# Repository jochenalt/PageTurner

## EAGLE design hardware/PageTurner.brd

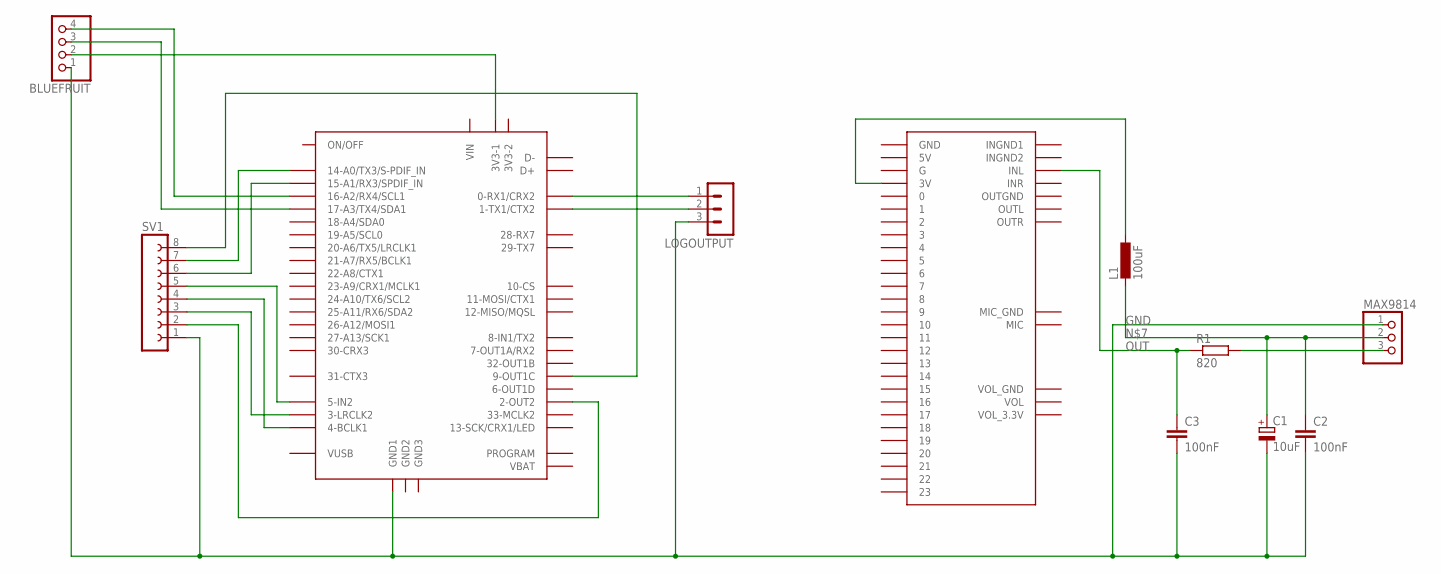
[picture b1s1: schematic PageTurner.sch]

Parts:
BLUEFRUIT: PINHD-1X4; 1X04
C1: 10uF; E2-4
C2, C3: 100nF; C025-040X050
L1: 100uF; 0207/5V
LOGOUTPUT: MA03-1
MAX9814: PINHD-1X3; 1X03
R1: 820; 0207/7
SV1: FE08-1; FE08
U$1: TEENSY40
U$2: AUDIOSHIELD

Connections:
3.3V: BLUEFRUIT.2, U$1.3V3-1
3V: L1.1, U$2.3V
BLE_RX: BLUEFRUIT.3, U$1.17-A3/TX4/SDA1
BLE_TX: BLUEFRUIT.4, U$1.16-A2/RX4/SCL1
GND: BLUEFRUIT.1, C1.-, C2.2, C3.2, LOGOUTPUT.3, MAX9814.1, SV1.1, U$1.GND1
unnamed: SV1.2, U$1.2-OUT2
unnamed: SV1.8, U$1.9-OUT1C
unnamed: MAX9814.3, R1.2
unnamed: SV1.3, U$1.3-LRCLK2
unnamed: C1.+, C2.1, L1.2, MAX9814.2
unnamed: LOGOUTPUT.1, U$1.0-RX1 (0-RX1/CRX2)
unnamed: SV1.4, U$1.4-BCLK2 (4-BCLK1)
unnamed: LOGOUTPUT.2, U$1.1-TX1 (1-TX1/CTX2)
unnamed: SV1.5, U$1.5-IN2
unnamed: SV1.6, U$1.15-A1/RX3/S-PDIF_IN (15-A1/RX3/SPDIF_IN)
OUT: C3.1, R1.1, U$2.INL

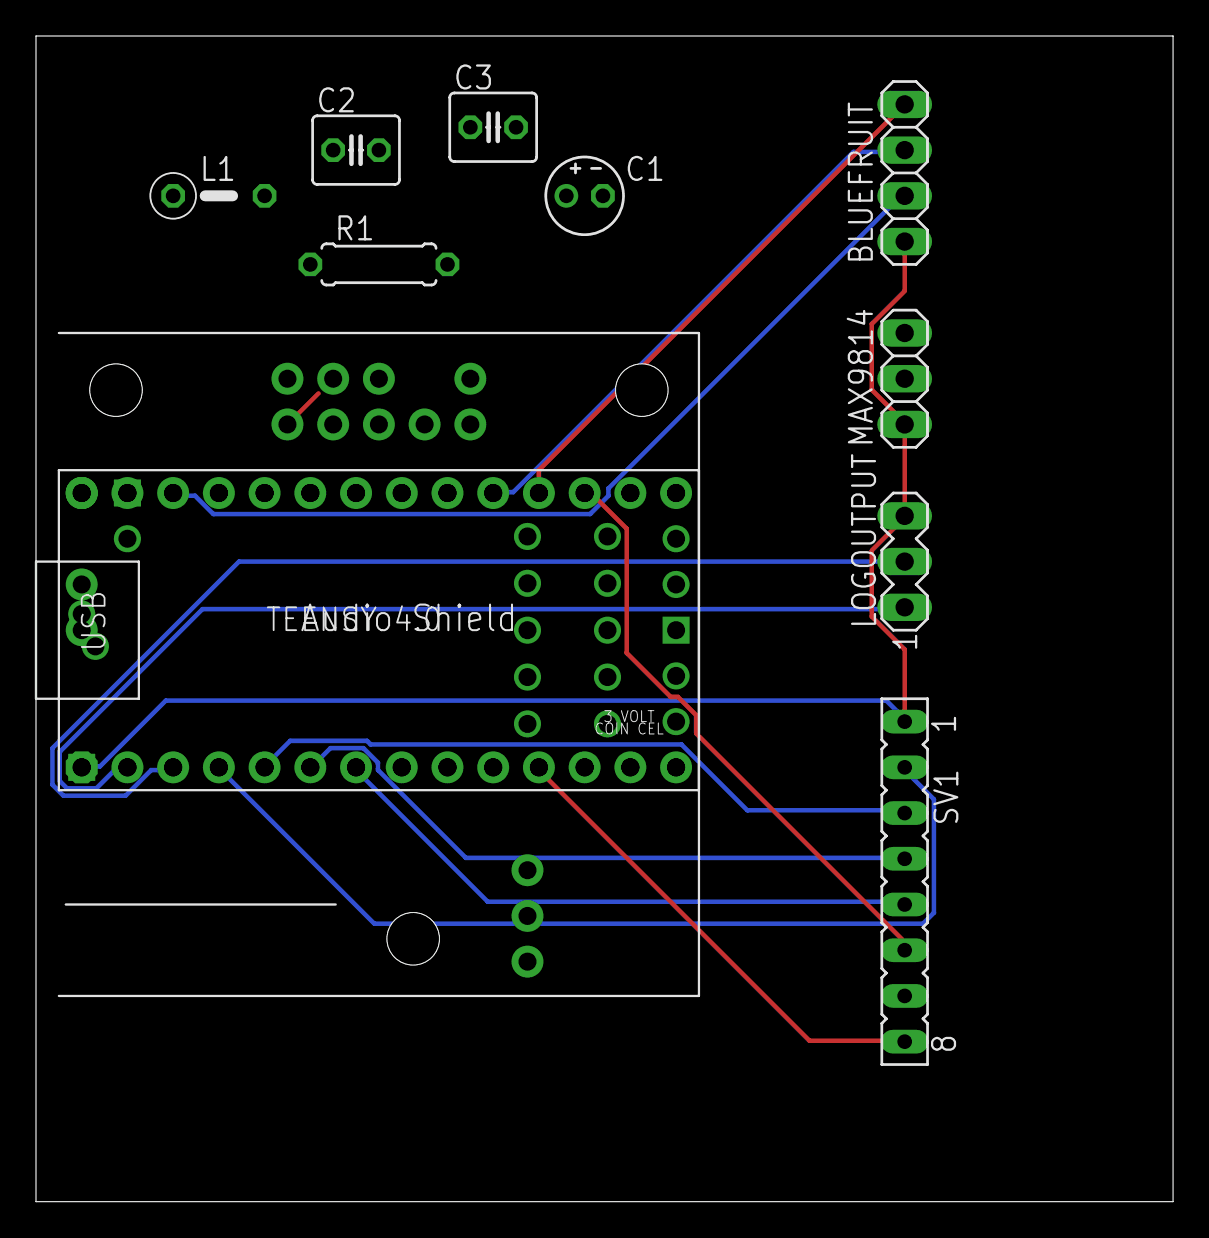
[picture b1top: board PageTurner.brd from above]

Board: 2 copper layers, 63.2 x 64.8 mm, 11 parts (0 on the bottom side), 16 nets.

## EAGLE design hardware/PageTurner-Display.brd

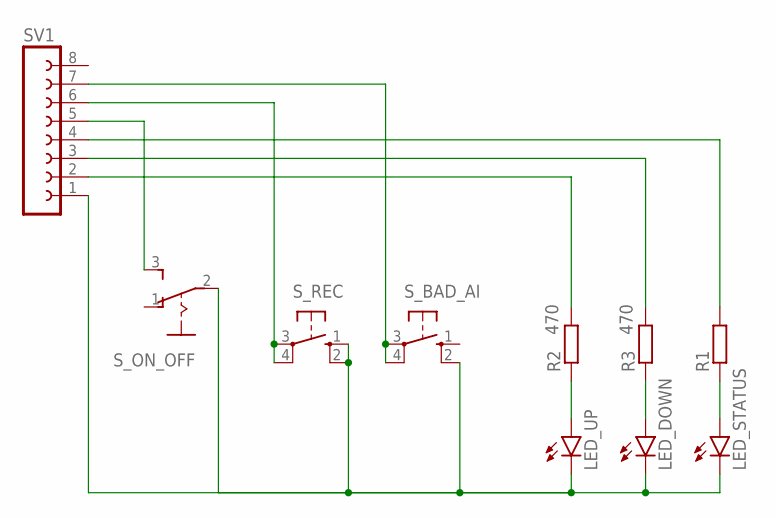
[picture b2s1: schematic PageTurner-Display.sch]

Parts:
LED_DOWN: LED3MM
LED_STATUS: LED3MM
LED_UP: LED3MM
R1, R2, R3: 470; 0207/12
SV1: FE08-1; FE08
S_BAD_AI: 10-XX; B3F-10XX
S_ON_OFF: 255SB
S_REC: 10-XX; B3F-10XX

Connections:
unnamed: SV1.7, S_BAD_AI.3, S_BAD_AI.4 (P1)
unnamed: SV1.5, S_ON_OFF.3 (S)
unnamed: LED_DOWN.A, R3.1
unnamed: LED_UP.A, R2.1
unnamed: LED_STATUS.A, R1.1
unnamed: LED_DOWN.K (C), LED_STATUS.K (C), LED_UP.K (C), SV1.1, S_BAD_AI.2 (S1), S_ON_OFF.2, S_REC.1 (S), S_REC.2 (S1)
unnamed: R2.2, SV1.2
unnamed: R1.2, SV1.4
unnamed: R3.2, SV1.3
unnamed: SV1.6, S_REC.3, S_REC.4 (P1)

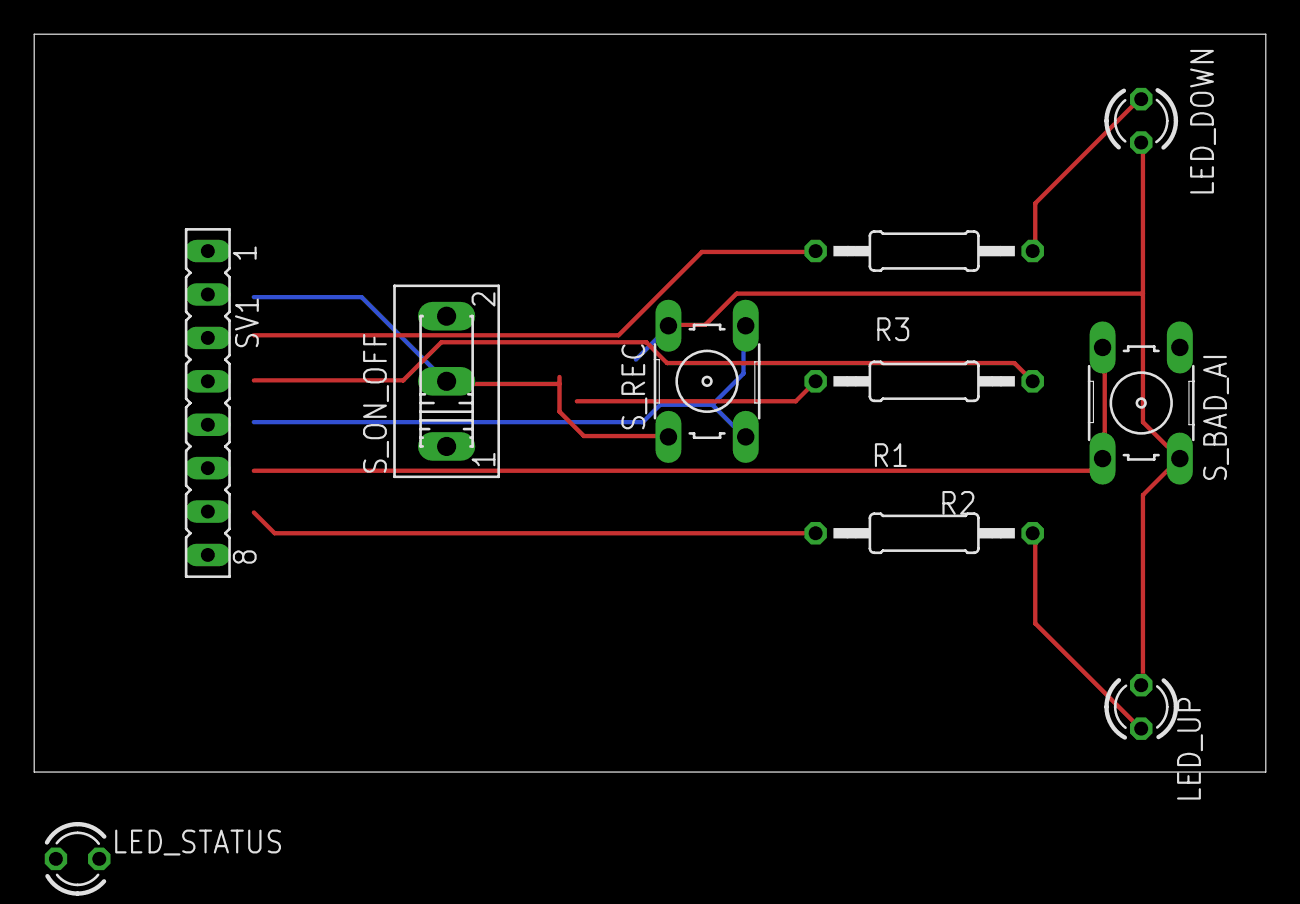
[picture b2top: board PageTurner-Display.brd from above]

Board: 2 copper layers, 72.1 x 43.2 mm, 10 parts (0 on the bottom side), 10 nets.

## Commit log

2025-06-12 init
2025-06-13 Mic input routed to headphones works
2025-06-13 Transfer to python program works
2025-06-14 Multiple recordings in a row
2025-06-14 Introduced 16KHz downsampling and augmentation
2025-06-14 renamed folder
2025-06-14 Training works now after an installation nighmaere trying to find out a tensorflow version that works
2025-06-14 evaluation mode in Teensy: long push turns on constant audio streaming
2025-06-14 introduced evaluatin mode that constante streams audio to Python
2025-06-15 removed training, switching tow edge impulse
2025-06-18 taking the edge impulse model, creating a C function running it, and creating a python script that records from the builtin microphone and pushes it through inference
2025-06-18 added a C function that returns all labels that have been defined in impulse edge
2025-06-19 added script pipeline
2025-06-20 moved everything to Ubuntu. Added inference mode from PC mic to trainer
2025-06-20 pushing recording button and running inference on python works now
2025-06-20 running inference on Teensy works now
2025-06-20 Teensy inference and c++ inference are sent to python and displayed
2025-06-21 little cleanup
2025-06-21 prepared production mode
2025-06-21 added active learning
2025-06-21 added run time inference (production mode)
2025-06-21 improved filter and inference
2025-06-21 buffer input audio instead of output audio to remove ticking
2025-06-21 added streaming mode for recording
2025-06-21 Bugfix im streaming mode
2025-06-21 added metronome
2025-06-22 tuned and cleaned up
2025-06-22 added Arduino version
2025-06-23 added silence check in which no inference happens and debounced pageup/pagedn accnounce by a min 1s break
2025-06-23 more debouncing and adjusted slience threshold
2025-06-27 preparations for futrue improvements
2025-06-27 repaired previous commit
2025-06-27 Introduced bad AI button
2025-06-27 Bluetooth almost working
2025-06-27 test bnew model
2025-06-28 Bluettooth works properly, LEDs reorganised
2025-06-28 pretty print
2025-06-28 updated Arduino library
2025-06-28 separated some AI classes for better recall
2025-07-01 restructured
2025-07-01 trained new model and made python programm not crashing if teensy connection breaks
2025-07-02 trained new model
2025-07-05 new teensy and audioboard and final display PCBs
2025-07-07 started feather
2025-07-08 blind coding of Tiny Turner
2025-07-08 new tt server
2025-07-08 webserver got the files per label
2025-07-08 new status line
2025-07-08 added training set optimisation function
2025-07-09 new website with webix started
2025-07-09 added corrected language labels in comboboxes
2025-07-09 Audio Box is filled now
2025-07-09 audio files can play now
2025-07-09 The play slider is now moving
2025-07-09 added creation of training set
2025-07-09 unit in display of seconds and samples
2025-07-10 got a feather, wifi configuration is working
2025-07-10 forgot to checkin battery
2025-07-10 CAD model of the box
2025-07-10 added terminal support
2025-07-10 new help menu item: reconfigure wifi
2025-07-11 added neopixel
2025-07-11 device information is sent
2025-07-11 allow to set a serial from menu
2025-07-11 fill labels with devices
2025-07-11 fill UI with device details
2025-07-11 changed owner combo box to label
2025-07-11 constructed a mirror to make use of the builtin neopixel
2025-07-12 added battery to CAD model
2025-07-12 removed command byte in http calls
2025-07-12 added call for sending sine wave
2025-07-12 add new recording fields
2025-07-12 fixed /api/device
2025-07-12 change name in recording box to "no label"
2025-07-12 added polling on website
2025-07-12 replaced polling by websockets
2025-07-12 concentrated websocket code
2025-07-12 added plaing recordings
2025-07-12 autoselect device if there is only one
2025-07-12 bugfix: Duration is not NaN anymore
